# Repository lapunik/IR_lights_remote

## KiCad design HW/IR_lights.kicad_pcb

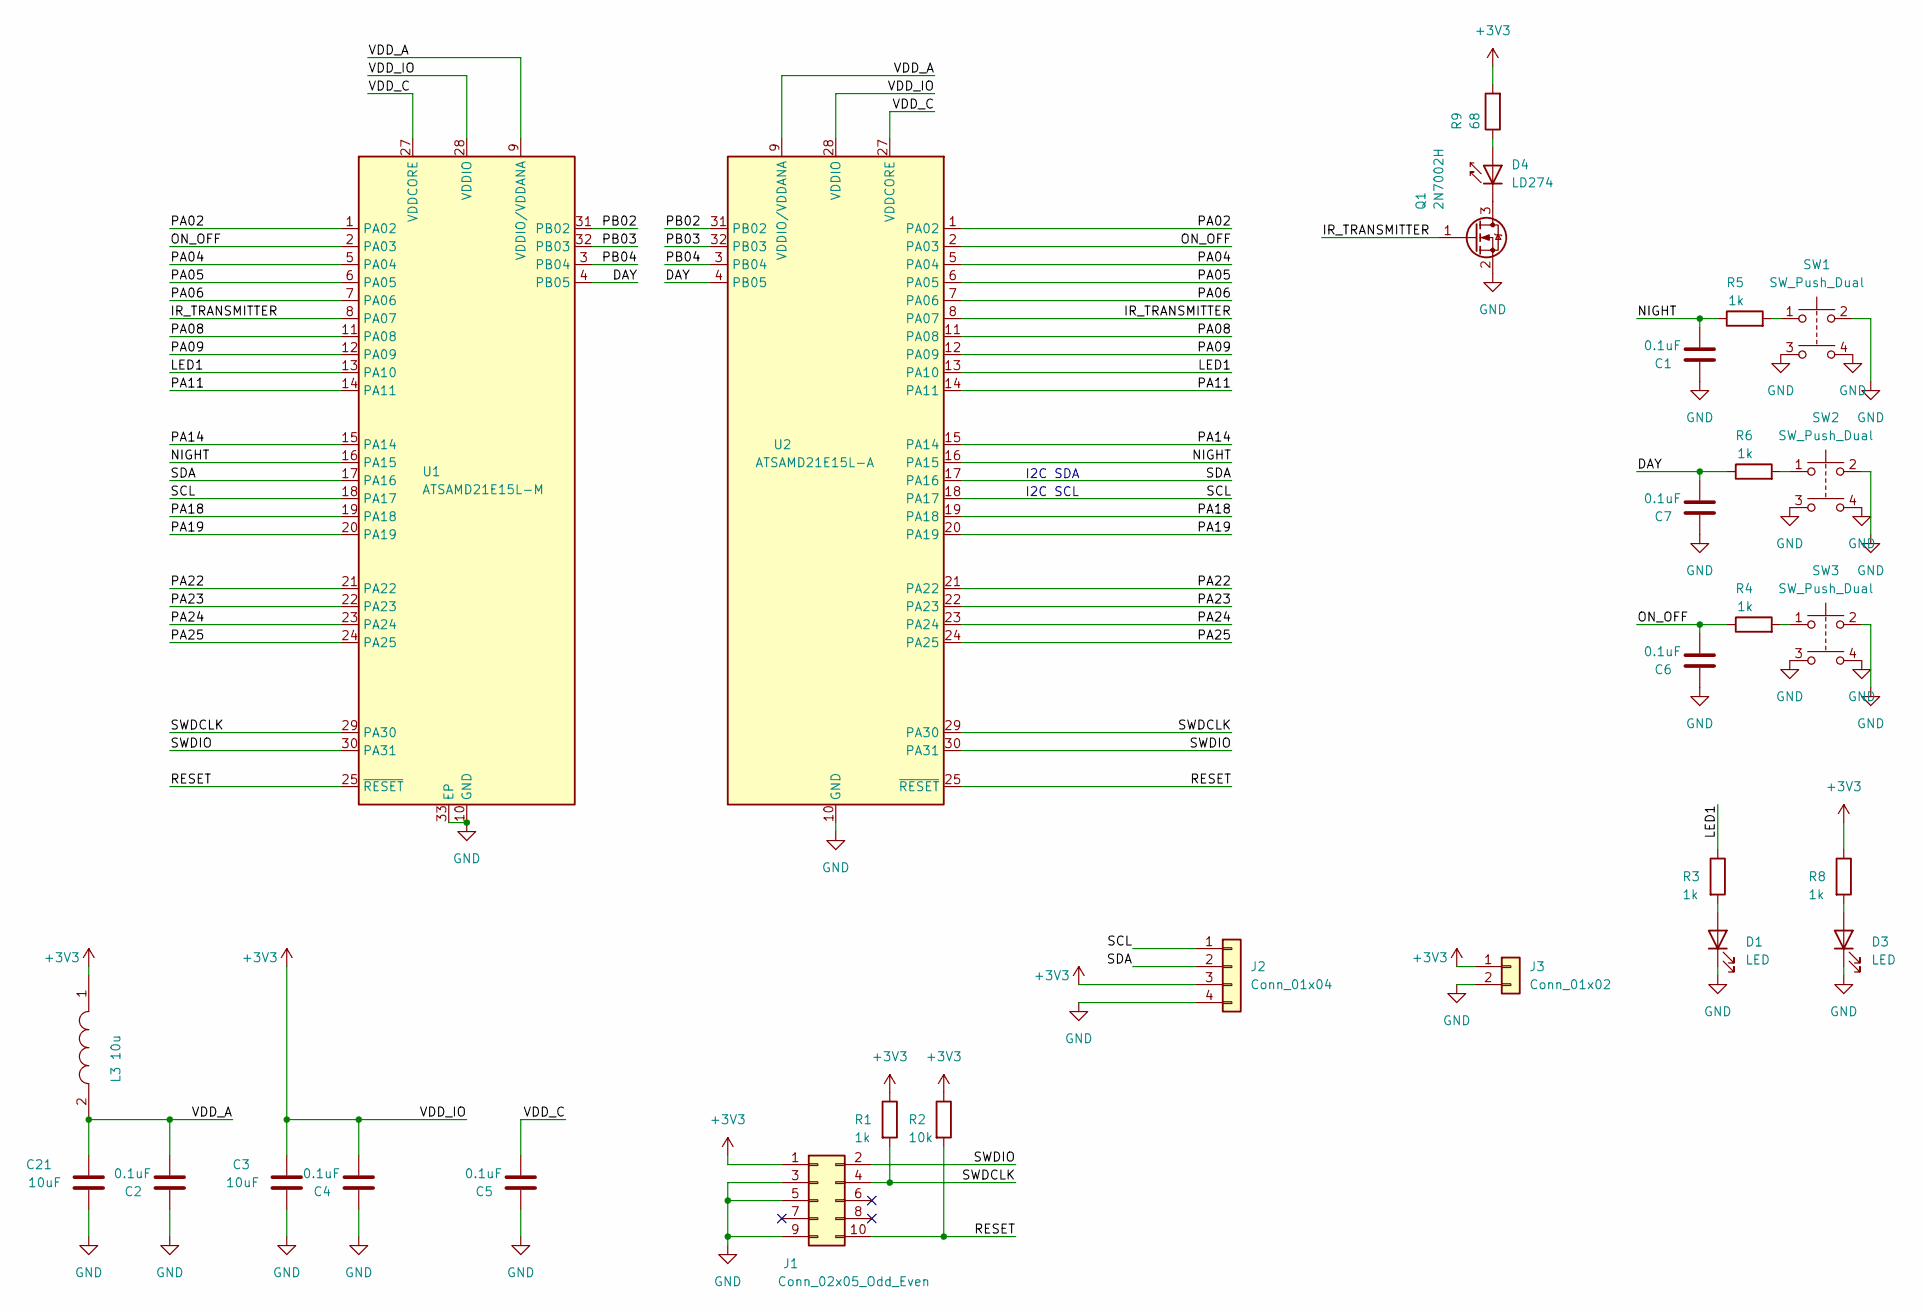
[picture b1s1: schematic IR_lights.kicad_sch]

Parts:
C1, C2, C4, C5, C6, C7: 0.1uF; C_0402_1005Metric
C3, C21: 10uF; C_0402_1005Metric
D1, D3: LED; LED_0402_1005Metric
D4: LD274; LED_D5.0mm_IRGrey
J1: Conn_02x05_Odd_Even; PinHeader_2x05_P1.27mm_Vertical
J2: Conn_01x04; PinHeader_1x04_P2.54mm_Horizontal
J3: Conn_01x02; PinHeader_1x02_P2.54mm_Vertical
L3: 10u; LQM21DN220N00L; Mouser Part Number 81-LQM21DH100M70L
Q1: 2N7002H; SOT-23
R1, R3, R4, R5, R6, R8: 1k; R_0402_1005Metric
R2: 10k; R_0402_1005Metric
R9: 68; R_0402_1005Metric
SW1, SW2, SW3: SW_Push_Dual; Tlacitko
U1: ATSAMD21E15L-M; QFN-32-1EP_5x5mm_P0.5mm_EP3.6x3.6mm
U2: ATSAMD21E15L-A; TQFP-32_7x7mm_P0.8mm

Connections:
+3V3: C3.2, C4.2, J1.1, J2.3, J3.1, L3.1, R1.1, R2.1, R8.1, R9.2, U1.28 (VDDIO), U2.28 (VDDIO)
/DAY: C7.2, R6.1, U1.4 (PB05), U2.4 (PB05)
/IR_TRANSMITTER: Q1.1 (G), U1.8 (PA07), U2.8 (PA07); also elsewhere on the board
/LED1: R3.1, U1.13 (PA10), U2.13 (PA10)
/NIGHT: C1.2, R5.1, U1.16 (PA15), U2.16 (PA15)
/ON_OFF: C6.2, R4.1, U1.2 (PA03), U2.2 (PA03)
/PA02: U1.1 (PA02), U2.1 (PA02)
/PA04: U1.5 (PA04), U2.5 (PA04)
/PA05: U1.6 (PA05), U2.6 (PA05)
/PA06: U1.7 (PA06), U2.7 (PA06)
/PA08: U1.11 (PA08), U2.11 (PA08)
/PA09: U1.12 (PA09), U2.12 (PA09)
/PA11: U1.14 (PA11), U2.14 (PA11)
/PA14: U1.15 (PA14), U2.15 (PA14)
/PA18: U1.19 (PA18), U2.19 (PA18)
/PA19: U1.20 (PA19), U2.20 (PA19)
/PA22: U1.21 (PA22), U2.21 (PA22)
/PA23: U1.22 (PA23), U2.22 (PA23)
/PA24: U1.23 (PA24), U2.23 (PA24)
/PA25: U1.24 (PA25), U2.24 (PA25)
/PB02: U1.31 (PB02), U2.31 (PB02)
/PB03: U1.32 (PB03), U2.32 (PB03)
/PB04: U1.3 (PB04), U2.3 (PB04)
/RESET: J1.10, R2.2, U1.25 (~RESET), U2.25 (~RESET)
/SCL: J2.1, U1.18 (PA17), U2.18 (PA17)
/SDA: J2.2, U1.17 (PA16), U2.17 (PA16)
/SWDCLK: J1.4, R1.2, U1.29 (PA30), U2.29 (PA30)
/SWDIO: J1.2, U1.30 (PA31), U2.30 (PA31)
/VDD_A: C2.2, C21.2, L3.2, U1.9 (VDDIO/VDDANA), U2.9 (VDDIO/VDDANA)
/VDD_C: C5.2, U1.27 (VDDCORE), U2.27 (VDDCORE)
GND: C1.1, C2.1, C3.1, C4.1, C5.1, C6.1, C7.1, C21.1, D1.1 (K), D3.1 (K), J1.3, J1.5, J1.9, J2.4, J3.2, Q1.2 (S), SW1.2, SW1.3, SW1.4, SW2.2, SW2.3, SW2.4, SW3.2, SW3.3, SW3.4, U1.10 (GND), U1.26 (GND), U1.33 (EP), U2.10 (GND), U2.26 (GND); also elsewhere on the board
unnamed: D1.2 (A), R3.2
unnamed: D3.2 (A), R8.2
unnamed: D4.1 (K), Q1.3 (D)
unnamed: D4.2 (A), R9.1
unnamed: R4.2, SW3.1
unnamed: R5.2, SW1.1
unnamed: R6.2, SW2.1

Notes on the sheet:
I2C SDA
I2C SCL

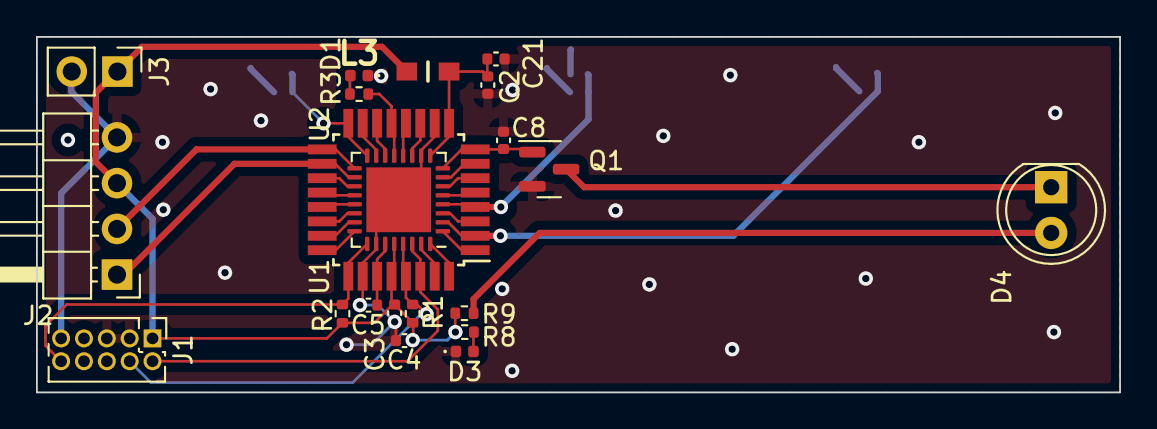
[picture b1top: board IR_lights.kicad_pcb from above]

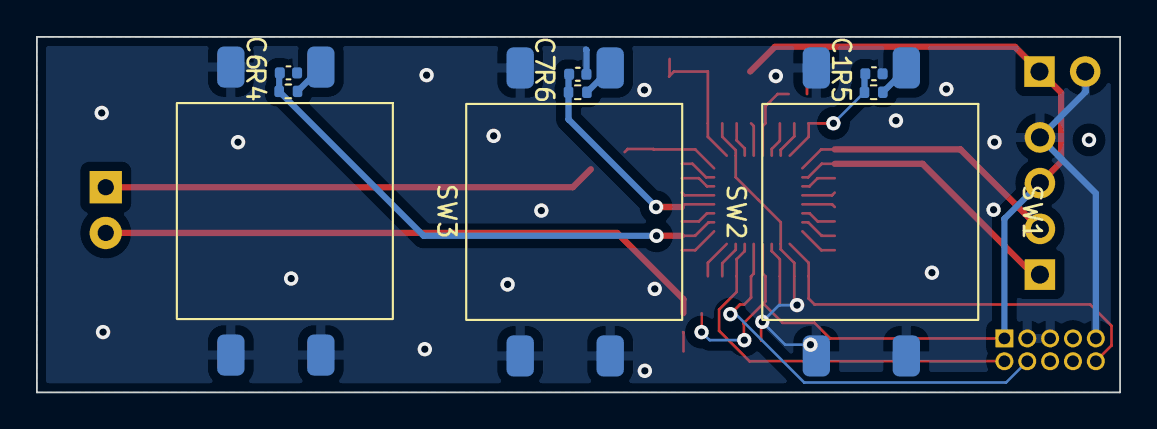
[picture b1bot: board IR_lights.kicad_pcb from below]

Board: 2 copper layers, 60.2 x 19.8 mm, 30 parts (9 on the bottom side), 38 nets.

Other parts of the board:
C8: 0.1uF; C_0402_1005Metric

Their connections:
/IR_TRANSMITTER: C8.2; also elsewhere on the board
GND: C8.1; also elsewhere on the board

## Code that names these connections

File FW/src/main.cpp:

#include <cstdint>
#include "sam.h"

#include "gpio.hpp"
#include "System.hpp"
#include "IR_transmitter.hpp"
#include "DS3231.hpp"
#include "Date_time.hpp"



using namespace nd::peripherals::gpio_pins; // abych mohl psát jen PAxx a nemusel vypisovt celou

nd::peripherals::Output_pin led1{pa10};

// IR sender
rg::IR_transmitter ir_sender{};

// Prevent use of malloc, new
extern "C" void *__wrap_malloc(std::size_t)
{
    return nullptr;
}
/*
void EIC_Handler()
{

   if(EIC->INTFLAG.bit.EXTINT3)
    {
        led1.on();
        ir_sender.send_code(rg::IR_transmitter::POWER);
        led1.off();
        EIC->INTFLAG.reg |= EIC_INTFLAG_EXTINT3;
    }
    else if(EIC->INTFLAG.bit.EXTINT5)
    {
        led1.on();
        ir_sender.send_code(rg::IR_transmitter::MID_BUTTON);
        led1.off();
        EIC->INTFLAG.reg |= EIC_INTFLAG_EXTINT5;
    }
    else if(EIC->INTFLAG.bit.EXTINT15)
    {
        led1.on();
        ir_sender.send_code(rg::IR_transmitter::EVENING);
        led1.off();
        EIC->INTFLAG.reg |= EIC_INTFLAG_EXTINT15;
    }
}*/
void main()
{
    SystemInit();

    nd::system::setup_oscilators(); // nastavení hodin (připojení a GCLK a připojení ke zdrojům hodin)
    nd::system::setup_peripherals_clocks(); // připojení některých periferií k hodinám (GCLK)

    // Buttons
    /*nd::peripherals::Alternate_pin on_off{pa03};
    //on_off.set_pull_up();
    //on_off.set_alternate_function(nd::peripherals::Gpio_alternate::A);
    //nd::peripherals::Alternate_pin night{pa15};
    //night.set_pull_up();
    //night.set_alternate_function(nd::peripherals::Gpio_alternate::A);
    //nd::peripherals::Alternate_pin day{pb05};
    //day.set_pull_up();
    //day.set_alternate_function(nd::peripherals::Gpio_alternate::A);
    */

    //nd::system::setup_interrupts();

    DS3231 rtc;
    rtc.init();

    //rtc.set_time();

    ir_sender.init();
    led1.off();

    //nd::system::enter_standby_mode();

    bool ledka = false;

#pragma clang diagnostic push
    #pragma ide diagnostic ignored "EndlessLoop"
    while (true)
    {

        //ir_sender.send_code(rg::IR_transmitter::POWER);

//        if((second % 5) == 0)
//        if(minute == 40)

    Date_time time;

    time = rtc.read_time();

    if(time.getMinute() == 26)
        {
            led1.on();

//            if(ledka)
//            {
//                led1.on();
//                ledka = false;
//            }
//            else
//            {
//                led1.off();
//                ledka = true;
//            }

        }
        else
        {
            led1.off();
        }

        nd::peripherals::systick::delay_ms(100,1);

        //nd::system::enter_standby_mode();
        /*
        if (!on_off.is_set())
        {
            while(!on_off.is_set());
            led1.on();
            ir_sender.send_code(rg::IR_transmitter::POWER);
            led1.off();
        }
        if (!day.is_set())
        {
            while(!day.is_set());
            led1.on();
            ir_sender.send_code(rg::IR_transmitter::MID_BUTTON);
            led1.off();
        }

        if (!night.is_set())
        {
            while(!night.is_set());
            led1.on();
            ir_sender.send_code(rg::IR_transmitter::EVENING);
            led1.off();
        }
        */


    }
    #pragma clang diagnostic pop
}

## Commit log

2023-03-30 Nahrani projektu
2023-04-03 Oprava proudu do IR lekdy + SDA,SDC
2023-04-08 Zmena otvoru pro uchyceni modulu
2023-04-08 SW v Arduino IDE
2023-05-12 Software v Clion
